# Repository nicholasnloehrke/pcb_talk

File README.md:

# Designing Printed Circuit Boards

## Scope
- Crash course for absolute beginners
- High level overview of the PCB design process

## What is a PCB?
- Mechanical structure
- Electrical connection

#### Single layer PCB 

> (https://manage.pcbgogo.com/img/js/ueditor/ueditor1.4.3.3/net/upload/image/20190927/6370519083456520006811116.png)

#### Multilayer PCB 

> (https://www.elecrow.com/media/wysiwyg/pcb/multilayer-PCB.jpg)

#### CNC Routing 

> (https://content.instructables.com/FAV/DW48/HHS9JZ8K/FAVDW48HHS9JZ8K.jpg?auto=webp&fit=bounds&frame=1&height=1024&width=1024)

#### PCBWay 

> (https://youtu.be/KKd_TkJRMAs?si=ITFjYFM6-m2PwDht&t=753)

## Designing a PCB
- Schematic capture
- Layout
- Manufacturing
- Assembly

### Lab 5 design

### Simplified design

### Kicad Schematic

### Kicad Layout

### Kicad 3D Render

### Tips
- Tutorials are great, but don't get stuck
- Datasheets are your friend
    - 
    - 
- ERC, DRC
- [Know when to care](https://saturnpcb.com/saturn-pcb-toolkit/)
    - Power
    - Frequency
- Verify footprints

## Resources
- [Kicad 7 YouTube tutorial](https://youtu.be/3FGNw28xBr0?si=RVbsRVqlHxJqC_zx)
- [Multipart Kicad 4 YouTube tutorial](https://youtu.be/vaCVh2SAZY4?si=ZYHfrUdhGqc2HB-z)

## Questions?

## Closing
- Contact info
    - loehrken@uwplatt.edu
- Further opportunities
    - https://github.com/nicholasnloehrke/87s_research
    -

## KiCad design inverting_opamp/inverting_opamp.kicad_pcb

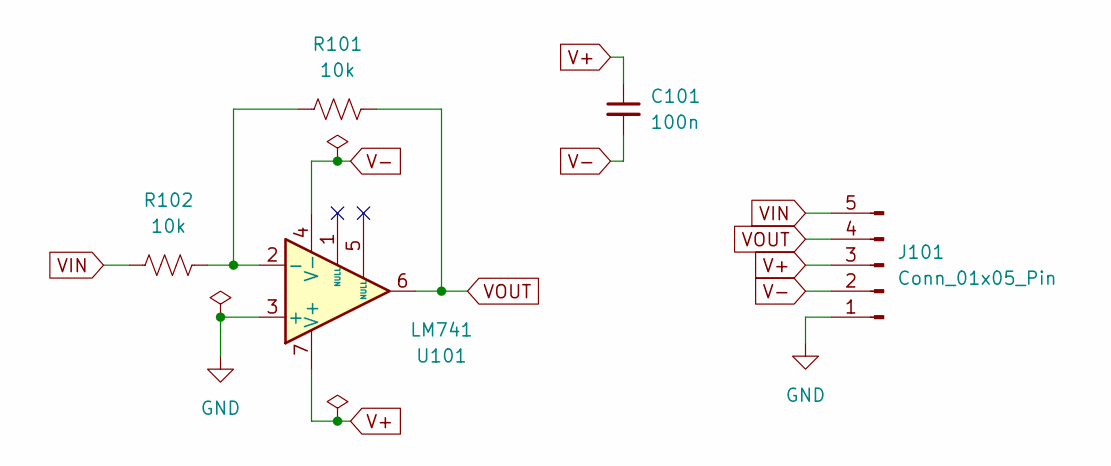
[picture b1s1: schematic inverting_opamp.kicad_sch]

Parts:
C101: 100n; C_Disc_D7.5mm_W2.5mm_P5.00mm
J101: Conn_01x05_Pin; PinHeader_1x05_P2.54mm_Vertical
R101, R102: 10k; R_Axial_DIN0207_L6.3mm_D2.5mm_P7.62mm_Horizontal
U101: LM741; DIP-8_W7.62mm

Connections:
GND: J101.1, U101.3 (+)
unnamed: R101.1, R102.2, U101.2 (-)
V+: C101.1, J101.3, U101.7 (V+)
V-: C101.2, J101.2, U101.4 (V-)
VIN: J101.5, R102.1
VOUT: J101.4, R101.2, U101.6

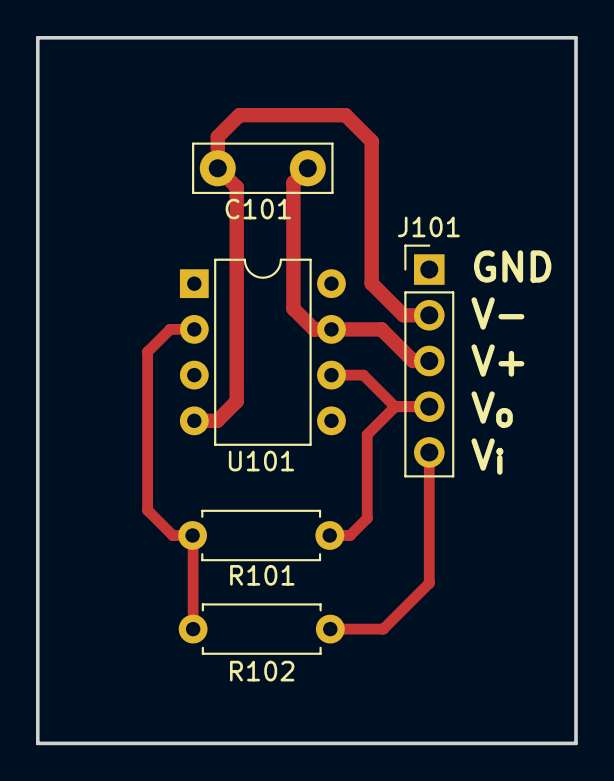
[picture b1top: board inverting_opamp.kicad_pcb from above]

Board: 2 copper layers, 29.9 x 39.2 mm, 5 parts (0 on the bottom side), 6 nets.

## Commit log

2024-12-02 init
2024-12-02 outline v2
2024-12-02 removed README
